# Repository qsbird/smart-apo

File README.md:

# Smart Apo · 智能阿波与智能水中

**想让浮漂自己记笔记，顺便查清是谁在拽鱼线。** 方案是水面阿波和钩侧水中件各记录一份数据，回收后对时分析。鱼还没参与测试，预算已经先替项目按了暂停键。

> [!NOTE]
> **项目状态：暂停。** 完整方案的预计试制成本超出当前预算。仓库保留研究过程与可审查的工程文件；暂停不等于技术验证通过。

> [!IMPORTANT]
> **制造状态：`NOT_FAB_RELEASED`。** Rev.A2 的 KiCad ERC 为 0 错误、0 警告，DRC 为 0 错误、0 未连接，仍有 **3 项连接区 courtyard 警告**。没有放行的生产 Gerber、钻孔和最终 BOM/CPL，也没有首件装配或水域实测。DRC 很能检查铜线，但不会替你拧紧 O 形圈。

## 先看钓组

*概念示意，不按比例。鱼在饵旁边，没有被画成“已咬钩”的成功案例；线长、结节、配重和安全绳位置仍需实物确认。*

| 设备 | 设计中的任务 | 主要硬件 |
|---|---|---|
| **阿波** · 水面 | 记录加速度、角速度和水压，原始数据写入本地 Flash；预留 LED 提示接口 | STM32G031、LSM6DSO、LPS28DFW、W25Q256、LiPo 供电/充电及 LED 驱动 |
| **智能水中** · 靠近钩侧 | 通过受力梁与应变全桥记录钓线张力，供回收后离线标注；也记录运动和压力 | 共用 MCU、IMU、压力传感器和 Flash，另装 316L 弹性梁、应变片全桥与 NAU7802 |

“共板”是**同一 PCB 设计、两块独立设备、两套贴装清单**。它们计划各自记录，回收后导出；水里不靠实时无线链路传数据。上表描述的是设计功能，尚无装配样机证明这些功能在水里运行。

## 波浪很会演，鱼却不一定配合

浮漂动了，原因可能是浪、流、提竿动作，也可能是钩侧发生了机械事件。这个项目希望用水中张力作研究阶段的辅助标签，寻找阿波的 IMU 与压力信号里可重复的特征，而不是只赌一个瞬时阈值。

```mermaid
flowchart LR
    A["阿波原始记录<br/>运动 · 压力"] -->|回收导出| H["主机工具<br/>校验 · 对时 · 评价"]
    U["水中原始记录<br/>张力 · 运动 · 压力"] -->|回收导出| H
    H --> P["候选检测参数"]
    P --> V["下一独立航次再验证"]
```

这条链路是研究方案，不是已经跑通的产品流程。尤其要说清楚：**张力变化说明钩侧受了力，不自动证明有鱼咬钩。** 摄像、提竿或捕获结果仍需作为语义真值。[现场验证计划](validation/FIELD_TEST_PLAN_CN.md)记录了拟进行的台架、水槽和真实海况测试。

## 尺寸和材料：设计目标，不是合格证

| 项目 | Rev.A 目标或候选 |
|---|---|
| 阿波外形 | 最大直径 32 mm、高 49 mm |
| 共用 PCB | 12 × 35 × 1.0 mm，四层，计划沉金 |
| 首批设想 | 共板 10 片，阿波和水中各装 5 套；**尚未下生产订单** |
| 电池 | 带保护 401020 LiPo，候选 60–80 mAh；所购型号与允许充电电流未锁定 |
| 深度 | 目标工作 10 m、15 m 等效静水压力验证；未实测 |
| 水中张力 | 目标工作 0–2 kgf；另需独立样件验证 ≥5 kgf 生存 |
| 受力件 | 0.30 mm 316L 弹性梁；打印件不能代替它承受钓线拉力 |

<details>
<summary>看看 Rev.A1 的机械概念预览</summary>

这张图展示壳体与梁的工程几何。梁 STL 只供看形状，真实受力件须按 [316L 加工规范](mechanical/316L_FLEXURE_SPEC_CN.md)和 DXF 制作；图像也不表示 Rev.A2 的装配干涉或防水测试通过。

</details>

位号、数量与 DNP 差异请看 [Rev.A2 工作 BOM](hardware/revA2/BOM_revA2_WORKING.csv)和[装配变体表](hardware/revA2/ASSEMBLY_VARIANTS_revA2.csv)。采购后缀与来料尚未全部确认，工作 BOM 不能直接当最终贴片清单。

## 进度条不如证据可靠

| 领域 | 已留下什么 | 还差什么 |
|---|---|---|
| **电路与 PCB** | Rev.A2 原理图、项目符号/封装库、四层已布线候选板；KiCad 10.0.6 官方 ERC 0/0、DRC 0 错误/0 未连接 | J1/J2/J3 的 3 项连接区 courtyard、所购器件与板厂工艺、完整 3D 装配审查和制造文件复核 |
| **主机数据工具** | UART 解码、CSV 输入校验、事件评分、离线寻参和合成数据生成 | 新航次头缺专门的 C→UART→Python 端到端验证；合成数据不能替代真实航次 |
| **MCU 固件** | 采样、Flash 日志、总线与时基源码；宿主模型测试 | 没有最终可烧录 ELF、板上运行、实测功耗或真正 Stop/RTC 闭环 |
| **机械** | Rev.A1 参数模型、STL、316L 梁 DXF 与装配说明 | 缺匹配 Rev.A2 的完整壳体/器件模型、实物干涉和密封验证 |
| **现场研究** | 静载、水槽、压力和真实海况试验计划 | 尚无可用于证明性能或可靠性的样机与实测数据 |

三处警告只是最显眼的剩余提示；更大的缺口在采购、装配和实物。详细情况见 [Rev.A2 交付门槛](hardware/revA2/DELIVERY_GATES_CURRENT_CN.md)与[暂停检查点](PAUSE_CHECKPOINT_20260924_CN.md)。历史检查点中的数字属于当时版本，别把不同日期的报告拼成一块“全绿”的板。

> [!CAUTION]
> `hardware/revA2/smart_apo_common_revA2.kicad_pcb` 是设计候选版；`hardware/` 根目录里早期的 `*_NETS_PLACED.kicad_pcb` 只是布局参考。**仓库里没有可直接付款投产的制造包。**

## 如果你想复现数字检查

在仓库根目录运行。Python 测试使用宿主机 C 编译器验证模型和协议，不能替代板上测试。

```bash
python3 -m unittest discover -s firmware/host/tests -v
python3 -m unittest discover -s firmware/mcu/tests -v
python3 -m unittest discover -s tools/tests -v
python3 tools/validate_revA2.py
```

2026-09-24 公开提交前，三组测试分别有 **34、8、17 项通过**，结构检查也通过；最新 UART 航次头尚缺完整端到端用例。若有 KiCad 10，可用仅检查模式刷新 ERC/DRC 报告：

```bash
KICAD_CLI=/path/to/kicad-cli bash tools/export_fab_revA2.sh --check-only
```

`--check-only` 会更新工程中的检查报告，不生成制造文件。返回 0 只说明脚本规定的电气门禁通过，**不替三处警告、采购、3D 和实物验证签字**。无参数调用会进入制造导出流程，当前项目不应将其结果视作放行。

安装了 NumPy、SciPy 后，还可以用合成数据熟悉离线工具：

```bash
python3 firmware/host/generate_synthetic_dataset.py
python3 firmware/host/autotune.py \
  firmware/host/example_data/awa.csv \
  firmware/host/example_data/underwater.csv \
  -o /tmp/smart-apo-synthetic-result.json
```

这个例子主要验证管线能否处理规定格式，不负责替鱼提供表演。真实数据的字段、缺测规则、时钟回绕与梁标定要求见 [主机说明](firmware/host/README_CN.md)和[数据协议](firmware/DATA_AND_AUTOTUNE_PROTOCOL_CN.md)。

## 仓库地图

```text
hardware/revA2/       当前原理图、PCB、项目库、工作 BOM、正式检查结果
hardware/*revA1*      Rev.A1 历史文件；旧板不能投产
firmware/mcu/         STM32 固件、宿主模型与构建说明
firmware/host/        解码、输入校验、评分和离线寻参
mechanical/           Rev.A1 壳体/托架、316L 梁图纸与装配说明
tools/                生成器、结构检查、BOM 检查、制造导出门禁
validation/           现场试验方案与 Rev.A1 验证记录
CONTEXT_HANDOFF.md    历史决策与交接资料
```

公开仓库保存源码、工程文件和正式检查结果。本机逐轮候选板、回退快照、编译日志及不完整 3D 审查包没有推送到 GitHub；旧文档提及这些目录时，请以仓库实际文件为准。

## 如果哪天预算松口

先补齐 UART 航次头的端到端测试和最终固件链接；再确认电芯、CT05、LED、晶振、MLCC、Pogo 与板厂工艺，关闭连接区警告；随后核对 Rev.A2 壳体/压力口/电池的实物干涉。完成制造文件独立审阅后，才轮到首件、梁标定、压力、盐水和水域试验。[PCB 放行清单](hardware/revA2/PCB_RELEASE_CHECKLIST_revA2_CN.md)给出了更细的关口。

**当前结论仍是：项目因成本超预算而暂停，Rev.A2 未制造放行。** 鱼可以晚点上钩，工程结论不能抢跑。

## 复用与交流

欢迎通过 Issue 指出具体器件、KiCad 位置或可重复的测试问题。仓库中由项目作者原创的代码、设计文件、文档与插图按 [WTFPL Version 2](LICENSE) 发布（SPDX：`WTFPL`）。引用或改作自第三方的器件资料、库内容等仍受其原有权利约束；本仓库的许可证不能替第三方授权。许可证也不等于产品安全或制造放行证明。

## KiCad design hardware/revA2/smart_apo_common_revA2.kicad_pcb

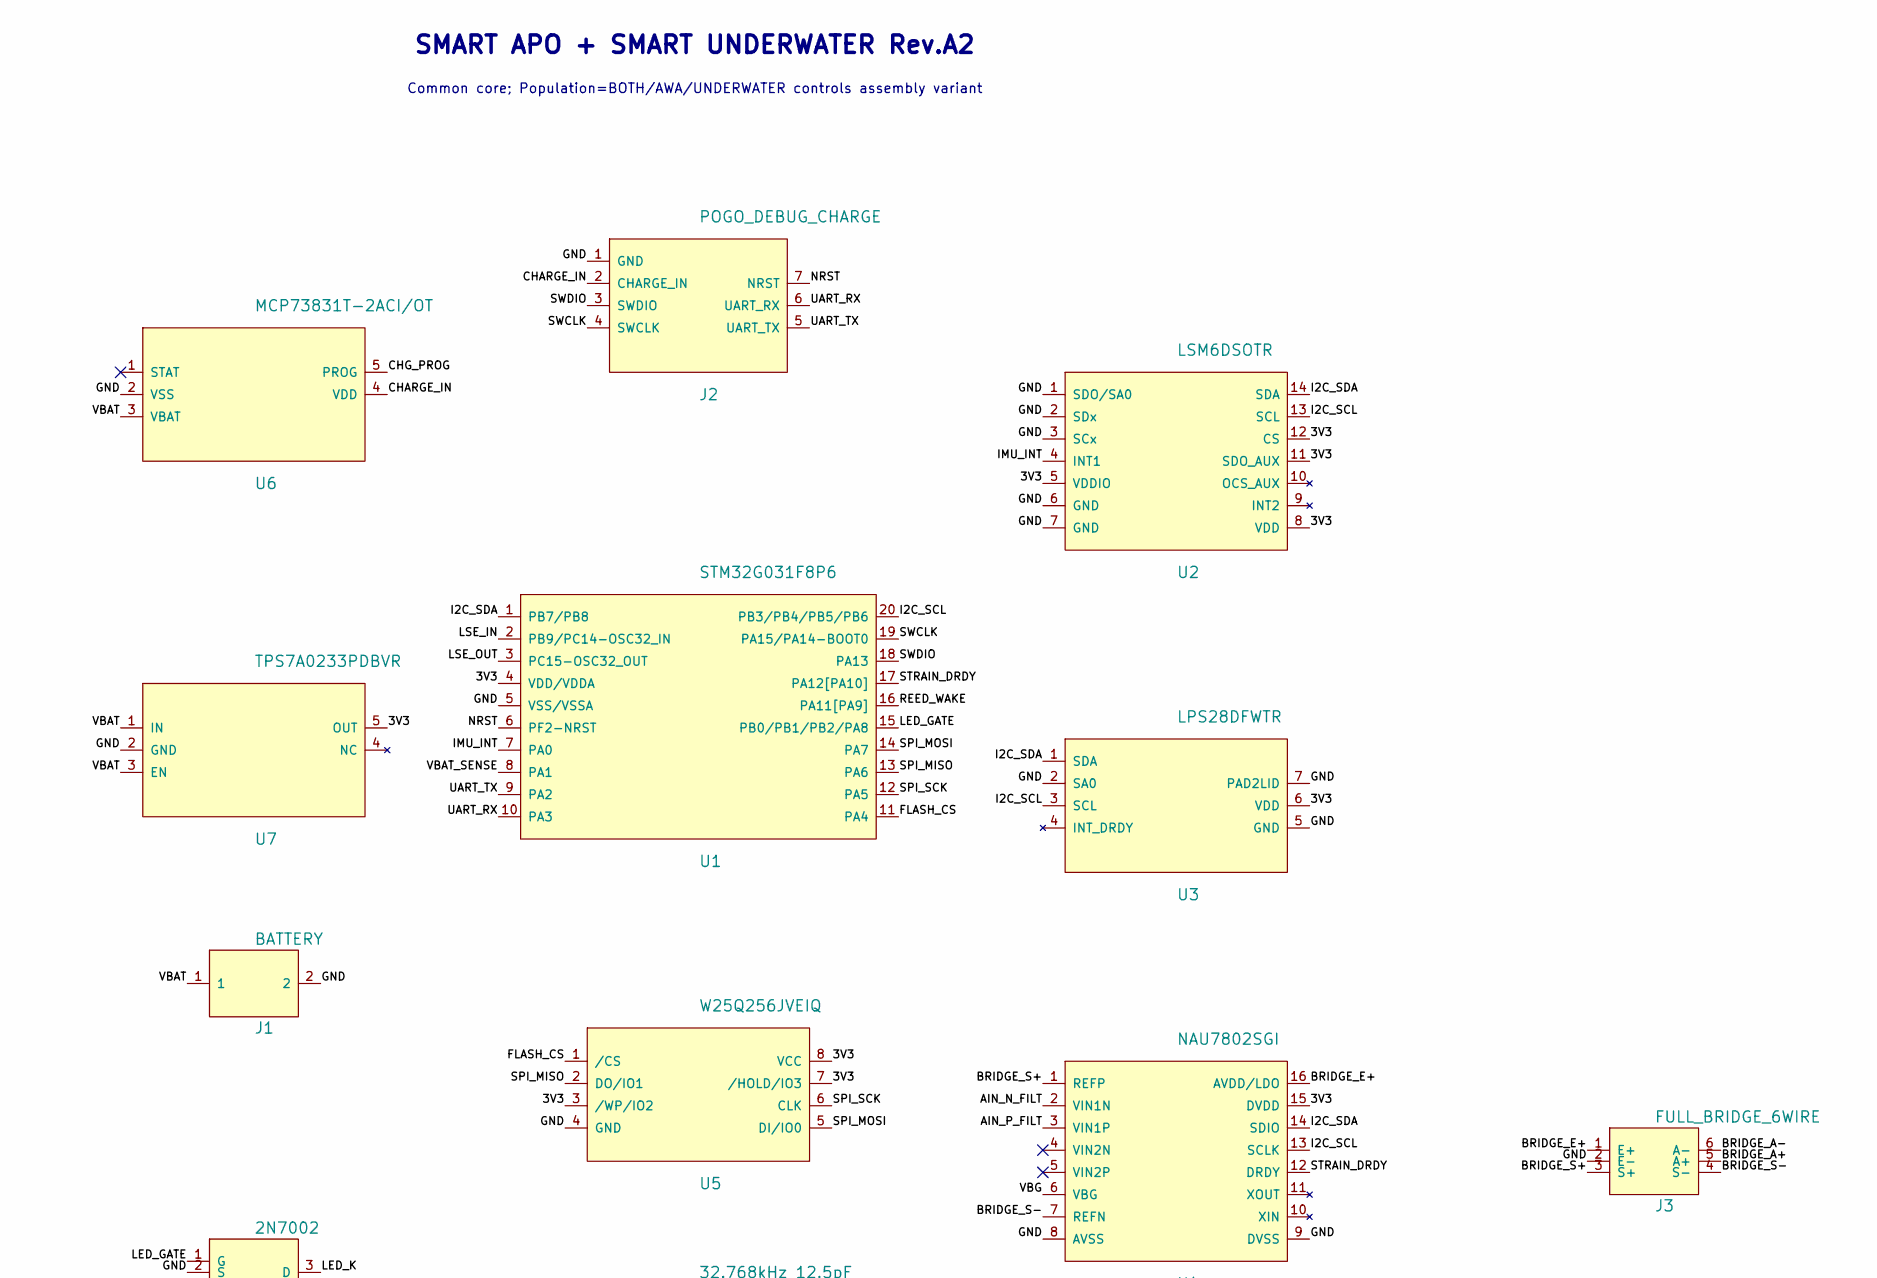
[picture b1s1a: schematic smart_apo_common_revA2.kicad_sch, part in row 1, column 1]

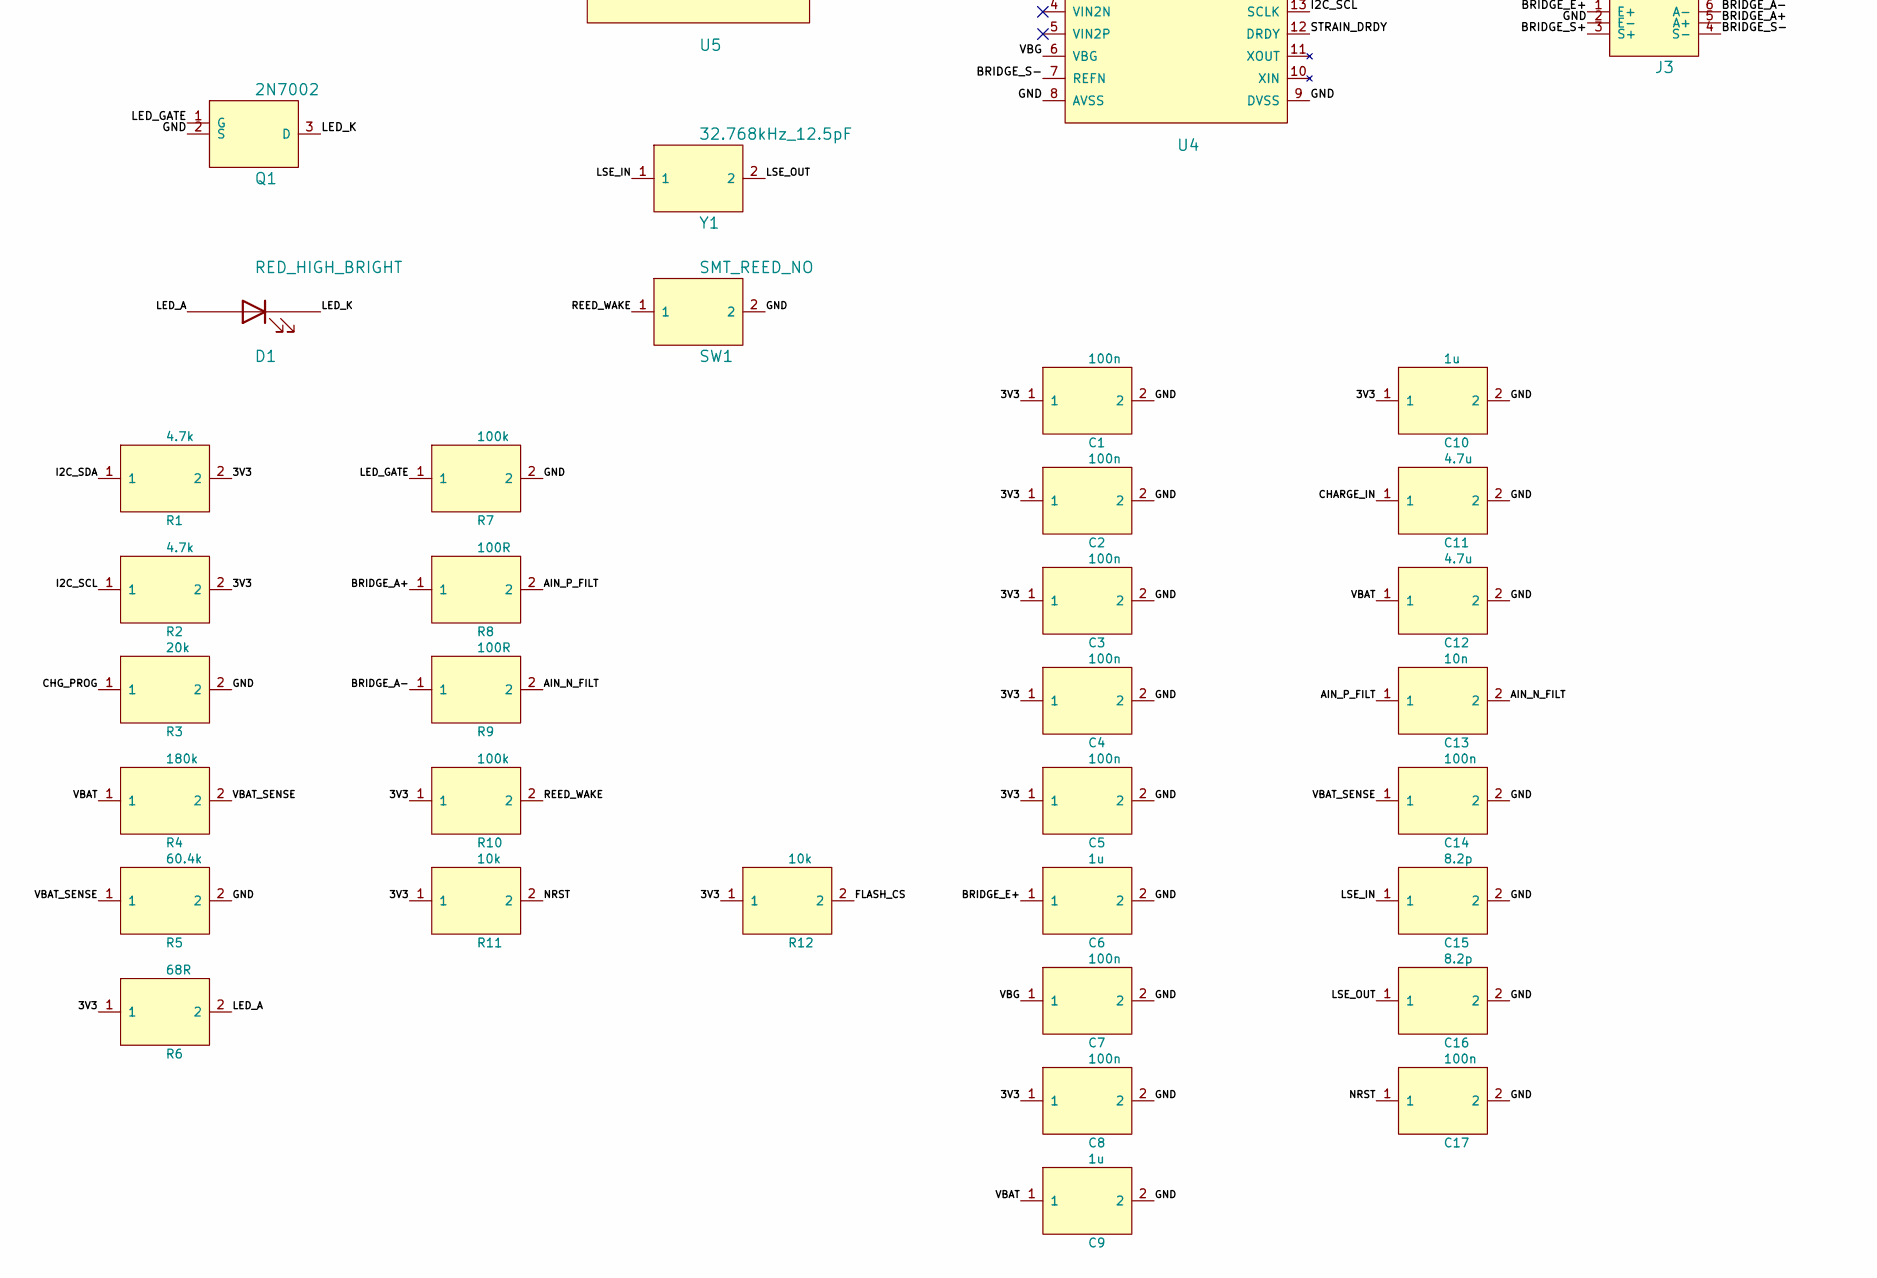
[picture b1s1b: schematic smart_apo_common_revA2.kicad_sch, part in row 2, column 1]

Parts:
C1, C2, C3, C4, C5, C7, C8, C14, C17: 100n; C_0402_1005Metric
C6, C9, C10: 1u; C_0402_1005Metric
C11, C12: 4.7u; C_0402_1005Metric
C13: 10n; C_0402_1005Metric
C15, C16: 8.2p; C_0402_1005Metric
D1: RED_HIGH_BRIGHT; LED_0805_2012Metric_RevA2_K1
J1: BATTERY; BATTERY_WIRE_PADS
J2: POGO_DEBUG_CHARGE; POGO_7x1.27mm
J3: FULL_BRIDGE_6WIRE; PAD_6x1.27mm
Q1: 2N7002; SOT-23
R1, R2: 4.7k; R_0402_1005Metric
R3: 20k; R_0402_1005Metric
R4: 180k; R_0402_1005Metric
R5: 60.4k; R_0402_1005Metric
R6: 68R; R_0402_1005Metric
R7, R10: 100k; R_0402_1005Metric
R8, R9: 100R; R_0402_1005Metric
R11, R12: 10k; R_0402_1005Metric
SW1: SMT_REED_NO; REED_CT05_COMPACT
U1: STM32G031F8P6; TSSOP-20_4.4x6.5mm_P0.65mm_RevA2_Pin1
U2: LSM6DSOTR; LGA-14_3x2.5mm_P0.5mm_LSM6DSO
U3: LPS28DFWTR; LPS28DFW_CCLGA-7L
U4: NAU7802SGI; SOIC-16_3.9x9.9mm_P1.27mm
U5: W25Q256JVEIQ; WSON-8_W25Q256JV_8x6mm_AN0000009
U6: MCP73831T-2ACI/OT; SOT-23-5
U7: TPS7A0233PDBVR; SOT-23-5
Y1: 32.768kHz_12.5pF; Crystal_SMD_2012-2Pin_2.0x1.2mm

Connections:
/3V3: C1.1, C2.1, C3.1, C4.1, C5.1, C8.1, C10.1, R1.2, R2.2, R6.1, R10.1, R11.1, R12.1, U1.4 (VDD/VDDA), U2.5 (VDDIO), U2.8 (VDD), U2.11 (SDO_AUX), U2.12 (CS), U3.6 (VDD), U4.15 (DVDD), U5.3 (/WP/IO2), U5.7 (/HOLD/IO3), U5.8 (VCC), U7.5 (OUT)
/AIN_N_FILT: C13.2, R9.2, U4.2 (VIN1N)
/AIN_P_FILT: C13.1, R8.2, U4.3 (VIN1P)
/BRIDGE_A+: J3.5 (A+), R8.1
/BRIDGE_A-: J3.6 (A-), R9.1
/BRIDGE_E+: C6.1, J3.1 (E+), U4.16 (AVDD/LDO)
/BRIDGE_S+: J3.3 (S+), U4.1 (REFP)
/BRIDGE_S-: J3.4 (S-), U4.7 (REFN)
/CHARGE_IN: C11.1, J2.2 (CHARGE_IN), U6.4 (VDD)
/CHG_PROG: R3.1, U6.5 (PROG)
/FLASH_CS: R12.2, U1.11 (PA4), U5.1 (/CS)
/GND: C1.2, C2.2, C3.2, C4.2, C5.2, C6.2, C7.2, C8.2, C9.2, C10.2, C11.2, C12.2, C14.2, C15.2, C16.2, C17.2, J1.2, J2.1 (GND), J3.2 (E-), Q1.2 (S), R3.2, R5.2, R7.2, SW1.2, U1.5 (VSS/VSSA), U2.1 (SDO/SA0), U2.2 (SDx), U2.3 (SCx), U2.6 (GND), U2.7 (GND), U3.2 (SA0), U3.5 (GND), U3.7 (PAD2LID), U4.8 (AVSS), U4.9 (DVSS), U5.4 (GND), U6.2 (VSS), U7.2 (GND)
/I2C_SCL: R2.1, U1.20 (PB3/PB4/PB5/PB6), U2.13 (SCL), U3.3 (SCL), U4.13 (SCLK)
/I2C_SDA: R1.1, U1.1 (PB7/PB8), U2.14 (SDA), U3.1 (SDA), U4.14 (SDIO)
/IMU_INT: U1.7 (PA0), U2.4 (INT1)
/LED_A: D1.2 (A), R6.2
/LED_GATE: Q1.1 (G), R7.1, U1.15 (PB0/PB1/PB2/PA8)
/LED_K: D1.1 (K), Q1.3 (D)
/LSE_IN: C15.1, U1.2 (PB9/PC14-OSC32_IN), Y1.1
/LSE_OUT: C16.1, U1.3 (PC15-OSC32_OUT), Y1.2
/NRST: C17.1, J2.7 (NRST), R11.2, U1.6 (PF2-NRST)
/REED_WAKE: R10.2, SW1.1, U1.16 (PA11[PA9])
/SPI_MISO: U1.13 (PA6), U5.2 (DO/IO1)
/SPI_MOSI: U1.14 (PA7), U5.5 (DI/IO0)
/SPI_SCK: U1.12 (PA5), U5.6 (CLK)
/STRAIN_DRDY: U1.17 (PA12[PA10]), U4.12 (DRDY)
/SWCLK: J2.4 (SWCLK), U1.19 (PA15/PA14-BOOT0)
/SWDIO: J2.3 (SWDIO), U1.18 (PA13)
/UART_RX: J2.6 (UART_RX), U1.10 (PA3)
/UART_TX: J2.5 (UART_TX), U1.9 (PA2)
/VBAT: C9.1, C12.1, J1.1, R4.1, U6.3 (VBAT), U7.1 (IN), U7.3 (EN)
/VBAT_SENSE: C14.1, R4.2, R5.1, U1.8 (PA1)
/VBG: C7.1, U4.6 (VBG)

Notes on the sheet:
SMART APO + SMART UNDERWATER Rev.A2
Common core; Population=BOTH/AWA/UNDERWATER controls assembly variant

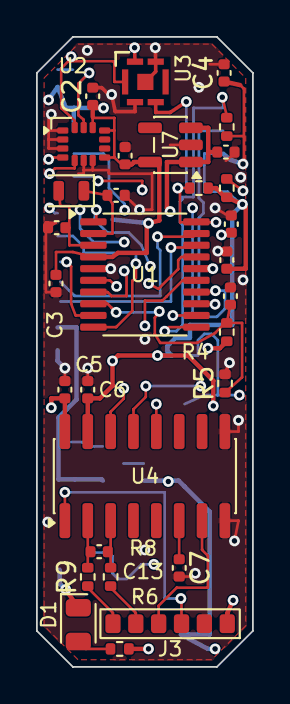
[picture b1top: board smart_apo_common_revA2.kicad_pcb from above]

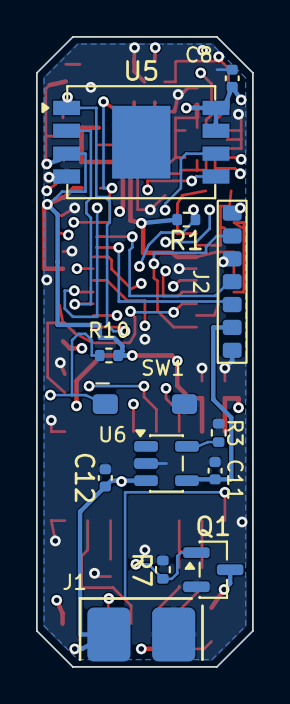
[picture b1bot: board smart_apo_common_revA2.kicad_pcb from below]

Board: 4 copper layers, 12.0 x 35.0 mm, 43 parts (13 on the bottom side), 33 nets.

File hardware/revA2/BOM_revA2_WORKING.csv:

Comment,Designator,Footprint,LCSC Part #,Manufacturer Part,AWA Qty,UNDERWATER Qty,Assembly,Notes
MCU,U1,SmartApoRevA2:TSSOP-20_4.4x6.5mm_P0.65mm_RevA2_Pin1,C529334,STM32G031F8P6,1,1,SMT,64KB Flash / 8KB RAM; stock must be rechecked at order
6-axis IMU,U2,SmartApoRevA2:LGA-14_3x2.5mm_P0.5mm_LSM6DSO,C2655100,LSM6DSOTR,1,1,SMT,Do not substitute without pin/driver review
Water-resistant pressure sensor,U3,SmartApoRevA2:LPS28DFW_CCLGA-7L,C3263277,LPS28DFWTR,1,1,SMT,Critical; footprint must be checked against ST TN0018
24-bit bridge ADC,U4,Package_SO:SOIC-16_3.9x9.9mm_P1.27mm,C5180029,NAU7802SGI,0,1,SMT,AVDD 3.0V; 320SPS; six-wire bridge
256Mbit SPI NOR,U5,SmartApoRevA2:WSON-8_W25Q256JV_8x6mm_AN0000009,C97522,W25Q256JVEIQ,1,1,SMT,Winbond AN0000009 p21 PCB land; C5334276 catalog MPN matches; incoming lot and carrier remain unverified
Li-ion charger,U6,Package_TO_SOT_SMD:SOT-23-5,C424093,MCP73831T-2ACI/OT,1,1,SMT,4.2V version; R3=20k gives nominal 50mA
3.3V LDO,U7,Package_TO_SOT_SMD:SOT-23-5,C2887324,TPS7A0233PDBVR,1,1,SMT,Alternate C5142805 TPS7A0233DBVR after review
N-MOSFET,Q1,Package_TO_SOT_SMD:SOT-23,,2N7002 or DMN1019USN-7,1,0,SMT,Lock JLC part during order
Red LED,D1,SmartApoRevA2:LED_0805_2012Metric_RevA2_K1,,High-bright red 0805,1,0,SMT,Optically couple to float light pipe
Battery pads,J1,SmartApoRevA2:BATTERY_WIRE_PADS,,BATTERY_WIRE_PADS,1,1,Manual,Protected 401020 LiPo 60-80mAh
Debug/charge pads,J2,SmartApoRevA2:POGO_7x1.27mm,,SWD_UART_CHARGE_POGO,1,1,PCB,No connector populated
Bridge pads,J3,SmartApoRevA2:PAD_6x1.27mm,,FULL_BRIDGE_6WIRE,0,1,Manual,E+/E-/S+/S-/A+/A-
Reed switch,SW1,SmartApoRevA2:REED_CT05_COMPACT,,Normally-open SMT reed,1,1,SMT,Wake input only; not in battery current path
32.768kHz crystal,Y1,Crystal:Crystal_SMD_2012-2Pin_2.0x1.2mm,,32.768kHz 12.5pF,1,1,SMT,Frequency tolerance <=20ppm preferred
4.7k 1%,R1 R2,Resistor_SMD:R_0402_1005Metric,,Generic thick film,2,2,SMT,I2C pullups
20k 1%,R3,Resistor_SMD:R_0402_1005Metric,,Generic thick film,1,1,SMT,Charge-program resistor
180k 1%,R4,Resistor_SMD:R_0402_1005Metric,,Generic thick film,1,1,SMT,Battery divider upper
60.4k 1%,R5,Resistor_SMD:R_0402_1005Metric,,Generic thick film,1,1,SMT,Battery divider lower
68R 1%,R6,Resistor_SMD:R_0402_1005Metric,,Generic thick film,1,0,SMT,LED series
100k 1%,R7,Resistor_SMD:R_0402_1005Metric,,Generic thick film,1,0,SMT,MOS gate pulldown
100R 0.1%,R8 R9,Resistor_SMD:R_0402_1005Metric,,Low-TCR precision resistor,0,2,SMT,Bridge differential input pair; same lot
100k 1%,R10,Resistor_SMD:R_0402_1005Metric,,Generic thick film,1,1,SMT,Reed pullup
10k 1%,R11,Resistor_SMD:R_0402_1005Metric,,Generic thick film,1,1,SMT,NRST pullup
10k 1%,R12,Resistor_SMD:R_0402_1005Metric,,Generic thick film,1,1,SMT,W25Q256 /CS reset-state pullup
100nF X7R,C1 C2 C3 C4 C5 C8 C14 C17,Capacitor_SMD:C_0402_1005Metric,,Generic MLCC,8,8,SMT,Rated >=10V; C14 tolerance <=20% (startup RC guard)
100nF X7R,C7,Capacitor_SMD:C_0402_1005Metric,,Generic MLCC,0,1,SMT,Underwater-only; matches formal schematic/PCB 100n; exact MPN and tolerance remain open
1uF X5R,C6 C9 C10,Capacitor_SMD:C_0402_1005Metric,,Generic MLCC,2,3,SMT,C6 underwater-only; C9/C10 common; effective capacitance under bias/temperature requires exact MPN review
4.7uF X5R,C11 C12,Capacitor_SMD:C_0402_1005Metric,,Generic MLCC,2,2,SMT,"Rated >=10V; actual PCB is 0402, not historical 0603; exact MPN/effective capacity and charge/LDO stability remain unverified"
10nF C0G,C13,Capacitor_SMD:C_0402_1005Metric,,Generic MLCC,0,1,SMT,Bridge differential filter
8.2pF C0G,C15 C16,Capacitor_SMD:C_0402_1005Metric,,Generic MLCC,2,2,SMT,Recalculate after crystal CL/parasitics review

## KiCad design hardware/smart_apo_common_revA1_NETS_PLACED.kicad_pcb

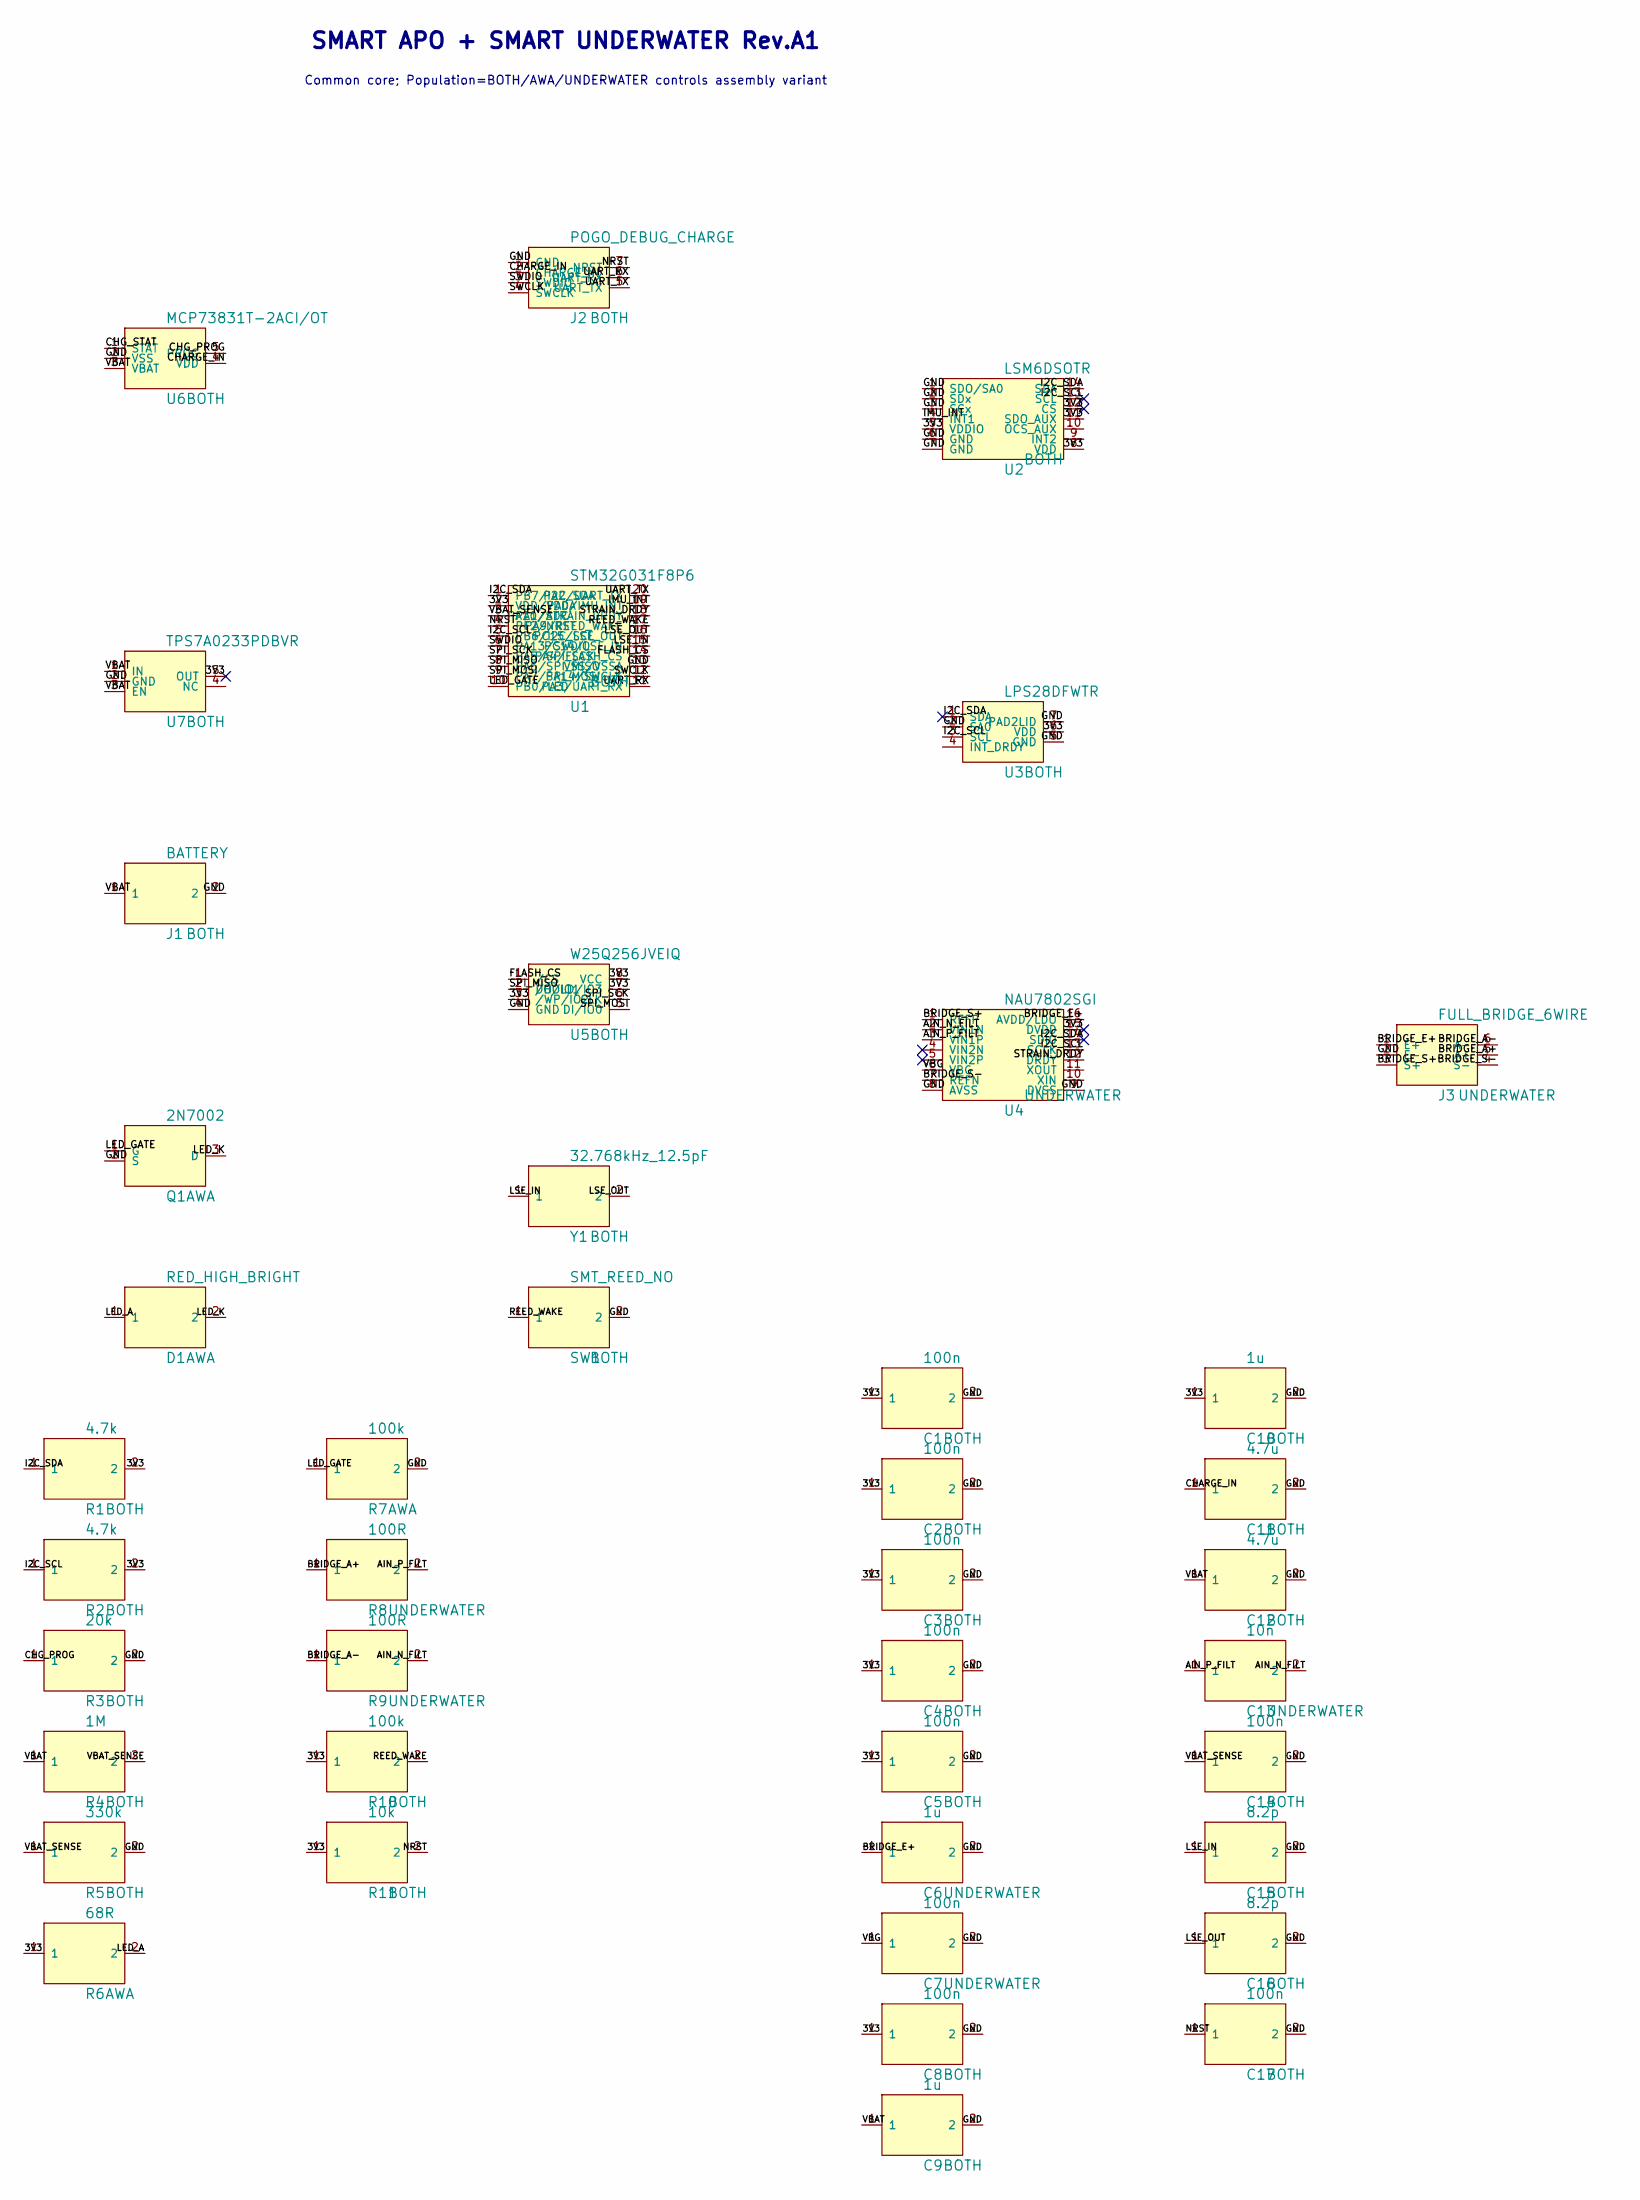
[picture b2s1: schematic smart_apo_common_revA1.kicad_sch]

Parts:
C1, C2, C3, C4, C5, C7, C8, C14, C17: 100n; C_0402_1005Metric
C6, C9, C10: 1u; C_0402_1005Metric
C11, C12: 4.7u; C_0402_1005Metric
C13: 10n; C_0402_1005Metric
C15, C16: 8.2p; C_0402_1005Metric
D1: RED_HIGH_BRIGHT; LED_0805_2012Metric
J1: BATTERY; SolderWire-1sqmm_1x02_P3.9mm_D1.4mm_OD2.7mm
J2: POGO_DEBUG_CHARGE; POGO_7x1.27mm
J3: FULL_BRIDGE_6WIRE; PAD_6x1.27mm
Q1: 2N7002; SOT-23
R1, R2: 4.7k; R_0402_1005Metric
R3: 20k; R_0402_1005Metric
R4: 1M; R_0402_1005Metric
R5: 330k; R_0402_1005Metric
R6: 68R; R_0402_1005Metric
R7, R10: 100k; R_0402_1005Metric
R8, R9: 100R; R_0402_1005Metric
R11: 10k; R_0402_1005Metric
SW1: SMT_REED_NO; SW_SPST_MK16
U1: STM32G031F8P6; TSSOP-20_4.4x6.5mm_P0.65mm
U2: LSM6DSOTR; LGA-14_2.5x3mm_P0.5mm
U3: LPS28DFWTR; CCLGA-7_LPS28DFW
U4: NAU7802SGI; SOIC-16_3.9x9.9mm_P1.27mm
U5: W25Q256JVEIQ; WSON-8-1EP_6x8mm_P1.27mm
U6: MCP73831T-2ACI/OT; SOT-23-5
U7: TPS7A0233PDBVR; SOT-23-5
Y1: 32.768kHz_12.5pF; Crystal_SMD_2012-2Pin_2.0x1.2mm

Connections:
3V3: C1.1, C2.1, C3.1, C4.1, C5.1, C8.1, C10.1, R1.2, R2.2, R6.1, R10.1, R11.1, U1.2 (VDD/VDDA), U2.5 (VDDIO), U2.8 (VDD), U2.11 (SDO_AUX), U2.12 (CS), U3.6 (VDD), U4.15 (DVDD), U5.3 (/WP/IO2), U5.7 (/HOLD/IO3), U5.8 (VCC), U7.5 (OUT)
AIN_N_FILT: C13.2, R9.2, U4.2 (VIN1N)
AIN_P_FILT: C13.1, R8.2, U4.3 (VIN1P)
BRIDGE_A+: J3.5 (A+), R8.1
BRIDGE_A-: J3.6 (A-), R9.1
BRIDGE_E+: C6.1, J3.1 (E+), U4.16 (AVDD/LDO)
BRIDGE_S+: J3.3 (S+), U4.1 (REFP)
BRIDGE_S-: J3.4 (S-), U4.7 (REFN)
CHARGE_IN: C11.1, J2.2 (CHARGE_IN), U6.4 (VDD)
CHG_PROG: R3.1, U6.5 (PROG)
CHG_STAT: U6.1 (STAT)
FLASH_CS: U1.14 (PA4/FLASH_CS), U5.1 (/CS)
GND: C1.2, C2.2, C3.2, C4.2, C5.2, C6.2, C7.2, C8.2, C9.2, C10.2, C11.2, C12.2, C14.2, C15.2, C16.2, C17.2, J1.2, J2.1 (GND), J3.2 (E-), Q1.2 (S), R3.2, R5.2, R7.2, SW1.2, U1.13 (VSS/VSSA), U2.1 (SDO/SA0), U2.2 (SDx), U2.3 (SCx), U2.6 (GND), U2.7 (GND), U3.2 (SA0), U3.5 (GND), U3.7 (PAD2LID), U4.8 (AVSS), U4.9 (DVSS), U5.4 (GND), U6.2 (VSS), U7.2 (GND)
I2C_SCL: R2.1, U1.5 (PB6/I2C_SCL), U2.13 (SCL), U3.3 (SCL), U4.13 (SCLK)
I2C_SDA: R1.1, U1.1 (PB7/I2C_SDA), U2.14 (SDA), U3.1 (SDA), U4.14 (SDIO)
IMU_INT: U1.19 (PA0/IMU_INT), U2.4 (INT1)
LED_A: D1.1, R6.2
LED_GATE: Q1.1 (G), R7.1, U1.10 (PB0/LED)
LED_K: D1.2, Q1.3 (D)
LSE_IN: C15.1, U1.15 (PC14/LSE_IN), Y1.1
LSE_OUT: C16.1, U1.16 (PC15/LSE_OUT), Y1.2
NRST: C17.1, J2.7 (NRST), R11.2, U1.4 (PF2/NRST)
REED_WAKE: R10.2, SW1.1, U1.17 (PA9/REED_WAKE)
SPI_MISO: U1.8 (PA6/SPI_MISO), U5.2 (DO/IO1)
SPI_MOSI: U1.9 (PA7/SPI_MOSI), U5.5 (DI/IO0)
SPI_SCK: U1.7 (PA5/SPI_SCK), U5.6 (CLK)
STRAIN_DRDY: U1.18 (PA10/STRAIN_DRDY), U4.12 (DRDY)
SWCLK: J2.4 (SWCLK), U1.12 (PA14/SWCLK)
SWDIO: J2.3 (SWDIO), U1.6 (PA13/SWDIO)
UART_RX: J2.6 (UART_RX), U1.11 (PA3/UART_RX)
UART_TX: J2.5 (UART_TX), U1.20 (PA2/UART_TX)
VBAT: C9.1, C12.1, J1.1, R4.1, U6.3 (VBAT), U7.1 (IN), U7.3 (EN)
VBAT_SENSE: C14.1, R4.2, R5.1, U1.3 (PA1/ADC)
VBG: C7.1, U4.6 (VBG)

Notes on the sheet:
SMART APO + SMART UNDERWATER Rev.A1
Common core; Population=BOTH/AWA/UNDERWATER controls assembly variant

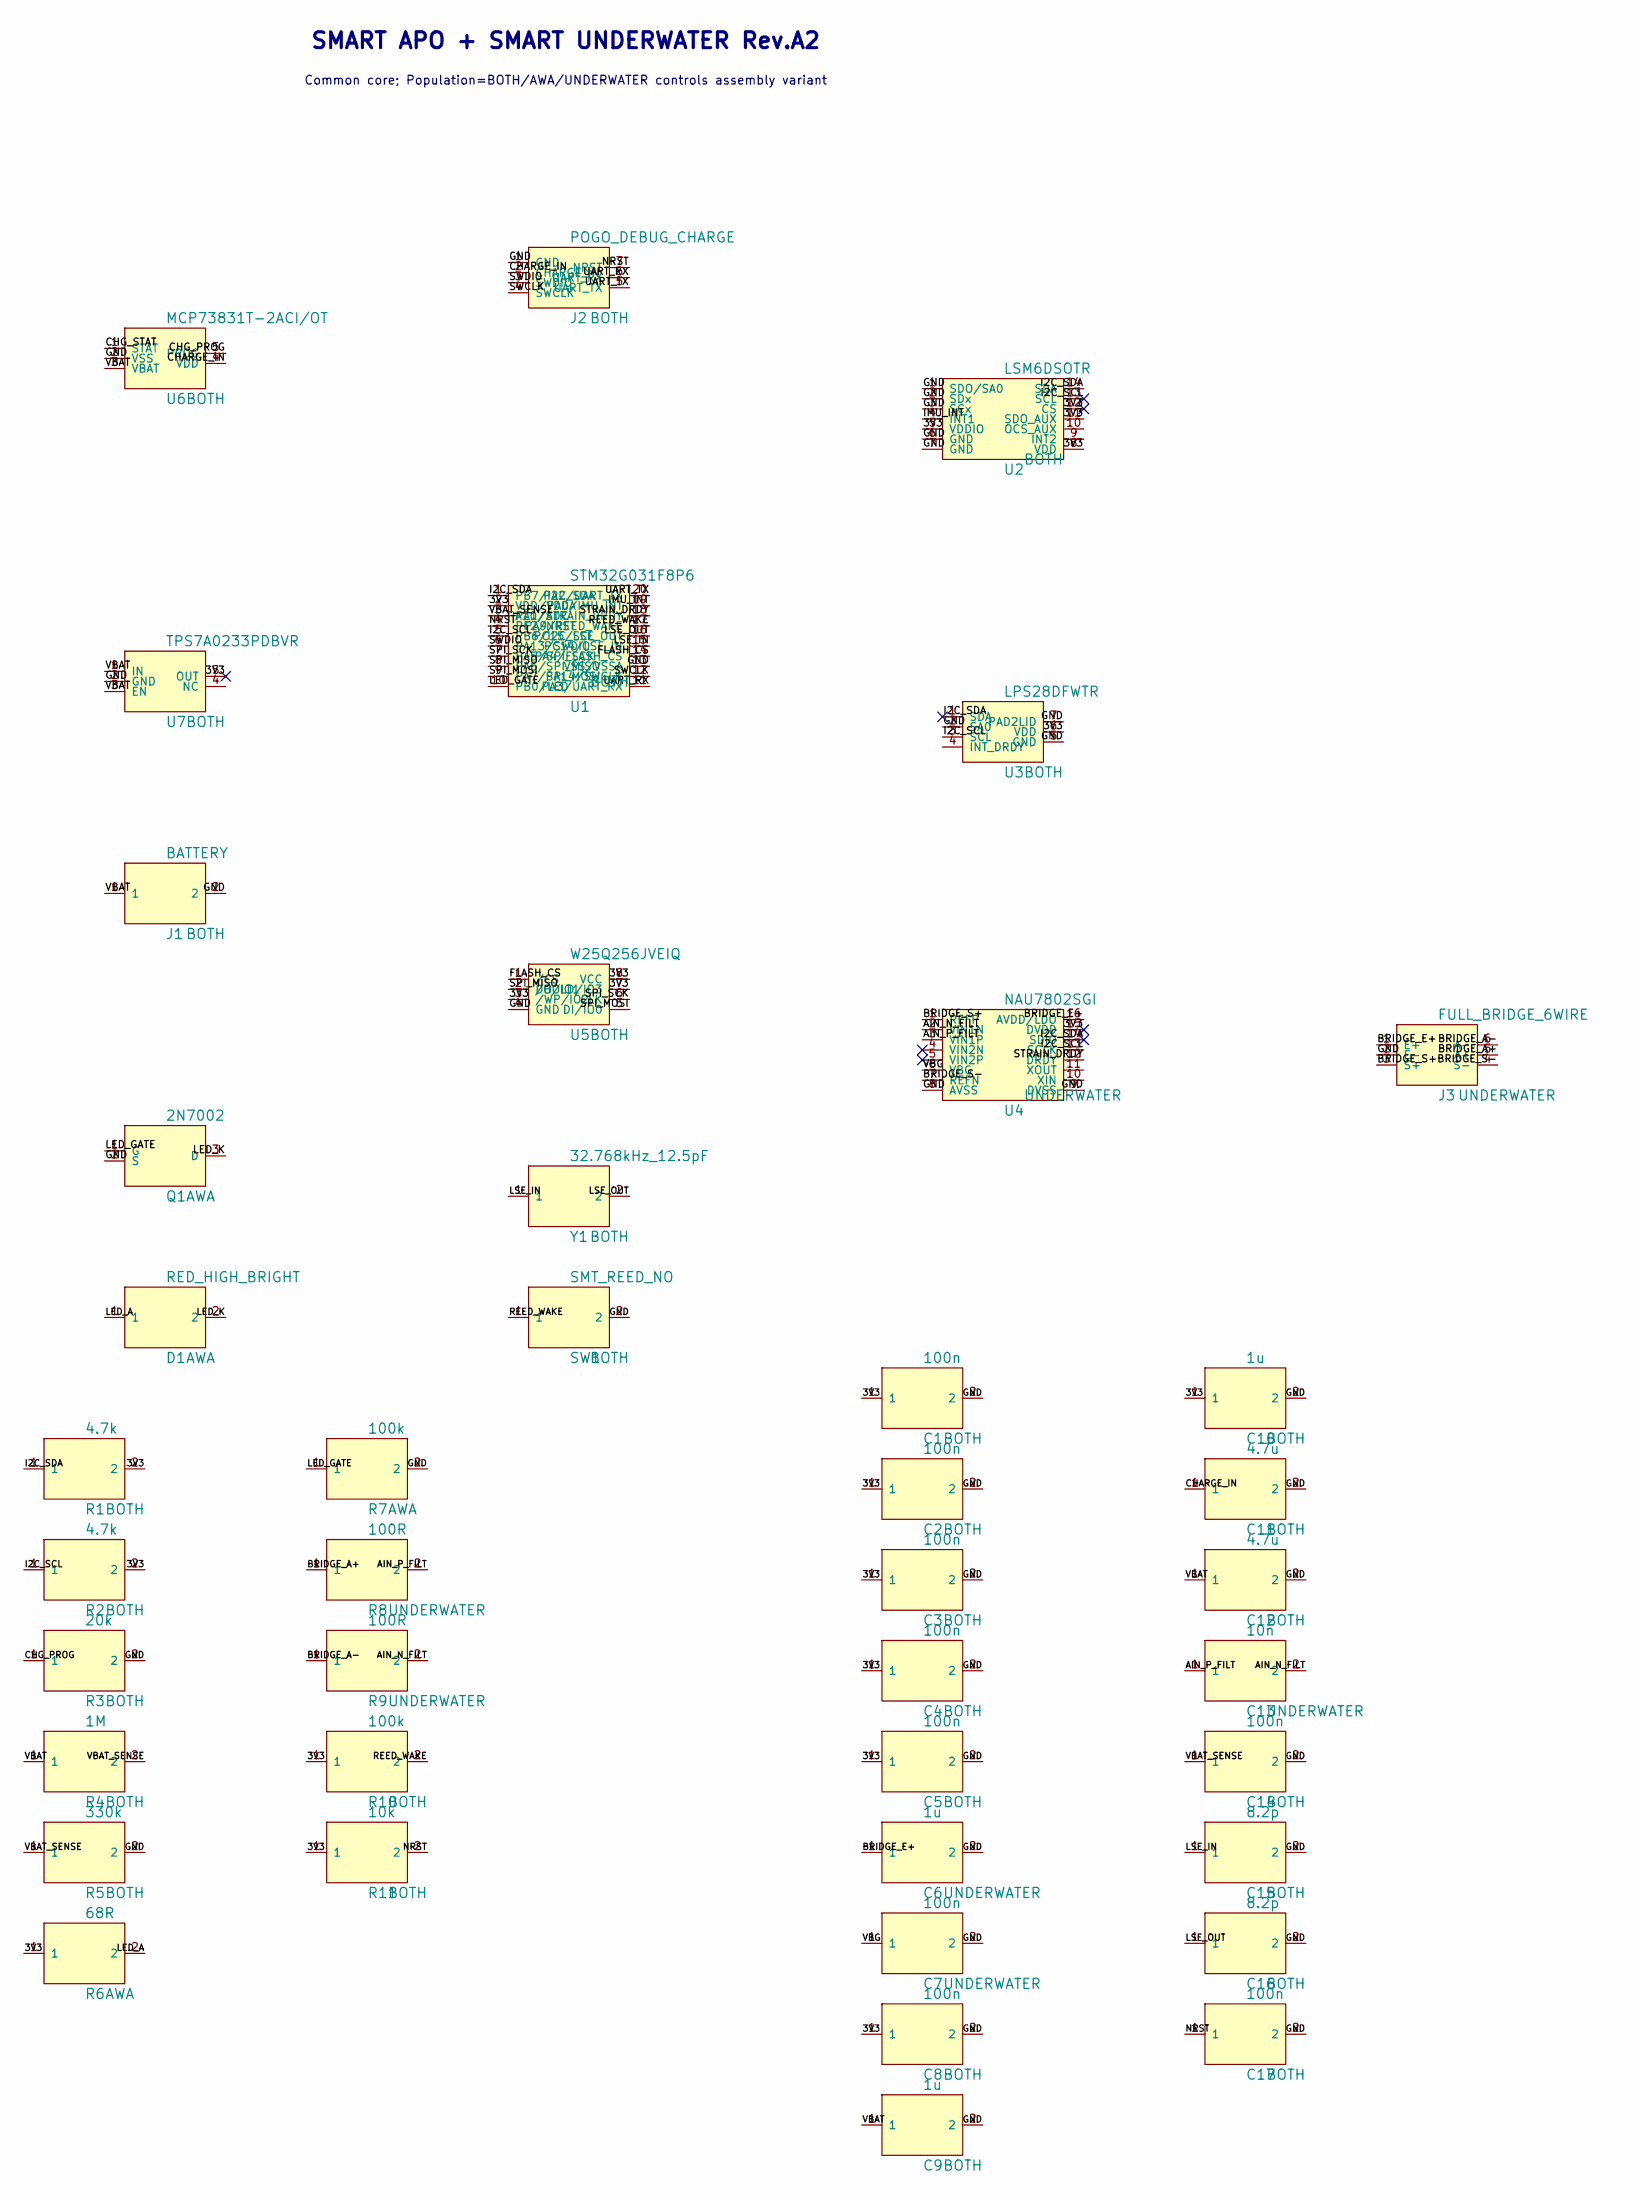
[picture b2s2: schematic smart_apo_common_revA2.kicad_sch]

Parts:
C1, C2, C3, C4, C5, C7, C8, C14, C17: 100n; C_0402_1005Metric
C6, C9, C10: 1u; C_0402_1005Metric
C11, C12: 4.7u; C_0402_1005Metric
C13: 10n; C_0402_1005Metric
C15, C16: 8.2p; C_0402_1005Metric
D1: RED_HIGH_BRIGHT; LED_0805_2012Metric
J1: BATTERY; SolderWire-1sqmm_1x02_P3.9mm_D1.4mm_OD2.7mm
J2: POGO_DEBUG_CHARGE; POGO_7x1.27mm
J3: FULL_BRIDGE_6WIRE; PAD_6x1.27mm
Q1: 2N7002; SOT-23
R1, R2: 4.7k; R_0402_1005Metric
R3: 20k; R_0402_1005Metric
R4: 1M; R_0402_1005Metric
R5: 330k; R_0402_1005Metric
R6: 68R; R_0402_1005Metric
R7, R10: 100k; R_0402_1005Metric
R8, R9: 100R; R_0402_1005Metric
R11: 10k; R_0402_1005Metric
SW1: SMT_REED_NO; SW_SPST_MK16
U1: STM32G031F8P6; TSSOP-20_4.4x6.5mm_P0.65mm
U2: LSM6DSOTR; LGA-14_2.5x3mm_P0.5mm
U3: LPS28DFWTR; CCLGA-7_LPS28DFW
U4: NAU7802SGI; SOIC-16_3.9x9.9mm_P1.27mm
U5: W25Q256JVEIQ; WSON-8-1EP_6x8mm_P1.27mm
U6: MCP73831T-2ACI/OT; SOT-23-5
U7: TPS7A0233PDBVR; SOT-23-5
Y1: 32.768kHz_12.5pF; Crystal_SMD_2012-2Pin_2.0x1.2mm

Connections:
3V3: C1.1, C2.1, C3.1, C4.1, C5.1, C8.1, C10.1, R1.2, R2.2, R6.1, R10.1, R11.1, U1.2 (VDD/VDDA), U2.5 (VDDIO), U2.8 (VDD), U2.11 (SDO_AUX), U2.12 (CS), U3.6 (VDD), U4.15 (DVDD), U5.3 (/WP/IO2), U5.7 (/HOLD/IO3), U5.8 (VCC), U7.5 (OUT)
AIN_N_FILT: C13.2, R9.2, U4.2 (VIN1N)
AIN_P_FILT: C13.1, R8.2, U4.3 (VIN1P)
BRIDGE_A+: J3.5 (A+), R8.1
BRIDGE_A-: J3.6 (A-), R9.1
BRIDGE_E+: C6.1, J3.1 (E+), U4.16 (AVDD/LDO)
BRIDGE_S+: J3.3 (S+), U4.1 (REFP)
BRIDGE_S-: J3.4 (S-), U4.7 (REFN)
CHARGE_IN: C11.1, J2.2 (CHARGE_IN), U6.4 (VDD)
CHG_PROG: R3.1, U6.5 (PROG)
CHG_STAT: U6.1 (STAT)
FLASH_CS: U1.14 (PA4/FLASH_CS), U5.1 (/CS)
GND: C1.2, C2.2, C3.2, C4.2, C5.2, C6.2, C7.2, C8.2, C9.2, C10.2, C11.2, C12.2, C14.2, C15.2, C16.2, C17.2, J1.2, J2.1 (GND), J3.2 (E-), Q1.2 (S), R3.2, R5.2, R7.2, SW1.2, U1.13 (VSS/VSSA), U2.1 (SDO/SA0), U2.2 (SDx), U2.3 (SCx), U2.6 (GND), U2.7 (GND), U3.2 (SA0), U3.5 (GND), U3.7 (PAD2LID), U4.8 (AVSS), U4.9 (DVSS), U5.4 (GND), U6.2 (VSS), U7.2 (GND)
I2C_SCL: R2.1, U1.5 (PB6/I2C_SCL), U2.13 (SCL), U3.3 (SCL), U4.13 (SCLK)
I2C_SDA: R1.1, U1.1 (PB7/I2C_SDA), U2.14 (SDA), U3.1 (SDA), U4.14 (SDIO)
IMU_INT: U1.19 (PA0/IMU_INT), U2.4 (INT1)
LED_A: D1.1, R6.2
LED_GATE: Q1.1 (G), R7.1, U1.10 (PB0/LED)
LED_K: D1.2, Q1.3 (D)
LSE_IN: C15.1, U1.15 (PC14/LSE_IN), Y1.1
LSE_OUT: C16.1, U1.16 (PC15/LSE_OUT), Y1.2
NRST: C17.1, J2.7 (NRST), R11.2, U1.4 (PF2/NRST)
REED_WAKE: R10.2, SW1.1, U1.17 (PA9/REED_WAKE)
SPI_MISO: U1.8 (PA6/SPI_MISO), U5.2 (DO/IO1)
SPI_MOSI: U1.9 (PA7/SPI_MOSI), U5.5 (DI/IO0)
SPI_SCK: U1.7 (PA5/SPI_SCK), U5.6 (CLK)
STRAIN_DRDY: U1.18 (PA10/STRAIN_DRDY), U4.12 (DRDY)
SWCLK: J2.4 (SWCLK), U1.12 (PA14/SWCLK)
SWDIO: J2.3 (SWDIO), U1.6 (PA13/SWDIO)
UART_RX: J2.6 (UART_RX), U1.11 (PA3/UART_RX)
UART_TX: J2.5 (UART_TX), U1.20 (PA2/UART_TX)
VBAT: C9.1, C12.1, J1.1, R4.1, U6.3 (VBAT), U7.1 (IN), U7.3 (EN)
VBAT_SENSE: C14.1, R4.2, R5.1, U1.3 (PA1/ADC)
VBG: C7.1, U4.6 (VBG)

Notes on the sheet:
SMART APO + SMART UNDERWATER Rev.A2
Common core; Population=BOTH/AWA/UNDERWATER controls assembly variant

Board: 4 copper layers, 42 parts (8 on the bottom side), 33 nets, no tracks yet.

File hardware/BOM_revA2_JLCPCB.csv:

Comment,Designator,Footprint,LCSC Part #,Manufacturer Part,AWA Qty,UNDERWATER Qty,Assembly,Notes
MCU,U1,TSSOP-20_4.4x6.5mm_P0.65,C529334,STM32G031F8P6,1,1,SMT,64KB Flash / 8KB RAM; stock must be rechecked at order
6-axis IMU,U2,LGA-14_2.5x3.0mm_P0.5,C2655100,LSM6DSOTR,1,1,SMT,Do not substitute without pin/driver review
Water-resistant pressure sensor,U3,CCLGA-7_2.8x2.8mm,C3263277,LPS28DFWTR,1,1,SMT,Critical; footprint must be checked against ST TN0018
24-bit bridge ADC,U4,SOIC-16_3.9x9.9mm_P1.27,C5180029,NAU7802SGI,0,1,SMT,AVDD 3.0V; 320SPS; six-wire bridge
256Mbit SPI NOR,U5,WSON-8_6x8mm_P1.27,C97522,W25Q256JVEIQ,1,1,SMT,Alternate C5334276 only after package check
Li-ion charger,U6,SOT-23-5,C424093,MCP73831T-2ACI/OT,1,1,SMT,4.2V version; R3=20k gives nominal 50mA
3.3V LDO,U7,SOT-23-5,C2887324,TPS7A0233PDBVR,1,1,SMT,Alternate C5142805 TPS7A0233DBVR after review
N-MOSFET,Q1,SOT-23,,2N7002 or DMN1019USN-7,1,0,SMT,Lock JLC part during order
Red LED,D1,LED_0805,,High-bright red 0805,1,0,SMT,Optically couple to float light pipe
Battery pads,J1,2-pad custom,,BATTERY_WIRE_PADS,1,1,Manual,Protected 401020 LiPo 60-80mAh
Debug/charge pads,J2,POGO_7x1.27mm,,SWD_UART_CHARGE_POGO,1,1,PCB,No connector populated
Bridge pads,J3,PAD_6x1.27mm,,FULL_BRIDGE_6WIRE,0,1,Manual,E+/E-/S+/S-/A+/A-
Reed switch,SW1,SMT reed 5mm,,Normally-open SMT reed,1,1,SMT,Wake input only; not in battery current path
32.768kHz crystal,Y1,2012-2P,,32.768kHz 12.5pF,1,1,SMT,Frequency tolerance <=20ppm preferred
4.7k 1%,R1 R2,0402,,Generic thick film,2,2,SMT,I2C pullups
20k 1%,R3,0402,,Generic thick film,1,1,SMT,Charge-program resistor
1M 1%,R4,0402,,Generic thick film,1,1,SMT,Battery divider upper
330k 1%,R5,0402,,Generic thick film,1,1,SMT,Battery divider lower
68R 1%,R6,0402,,Generic thick film,1,0,SMT,LED series
100k 1%,R7,0402,,Generic thick film,1,0,SMT,MOS gate pulldown
100R 0.1%,R8 R9,0402,,Low-TCR precision resistor,0,2,SMT,Bridge differential input pair; same lot
100k 1%,R10,0402,,Generic thick film,1,1,SMT,Reed pullup
10k 1%,R11,0402,,Generic thick film,1,1,SMT,NRST pullup
100nF X7R,C1 C2 C3 C4 C5 C8 C14 C17,0402,,Generic MLCC,8,8,SMT,Rated >=10V
1uF X5R,C6 C7 C9 C10,0402,,Generic MLCC,2,4,SMT,C6/C7 are underwater-only
4.7uF X5R,C11 C12,0603,,Generic MLCC,2,2,SMT,Rated >=10V
10nF C0G,C13,0402,,Generic MLCC,0,1,SMT,Bridge differential filter
8.2pF C0G,C15 C16,0402,,Generic MLCC,2,2,SMT,Recalculate after crystal CL/parasitics review
